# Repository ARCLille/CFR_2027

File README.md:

# CFR_2027
Repo de la coupe de France de Robotique 2027. Cartes électroniques, Firmware et Librairies.

**KiCAD version : 10.0**

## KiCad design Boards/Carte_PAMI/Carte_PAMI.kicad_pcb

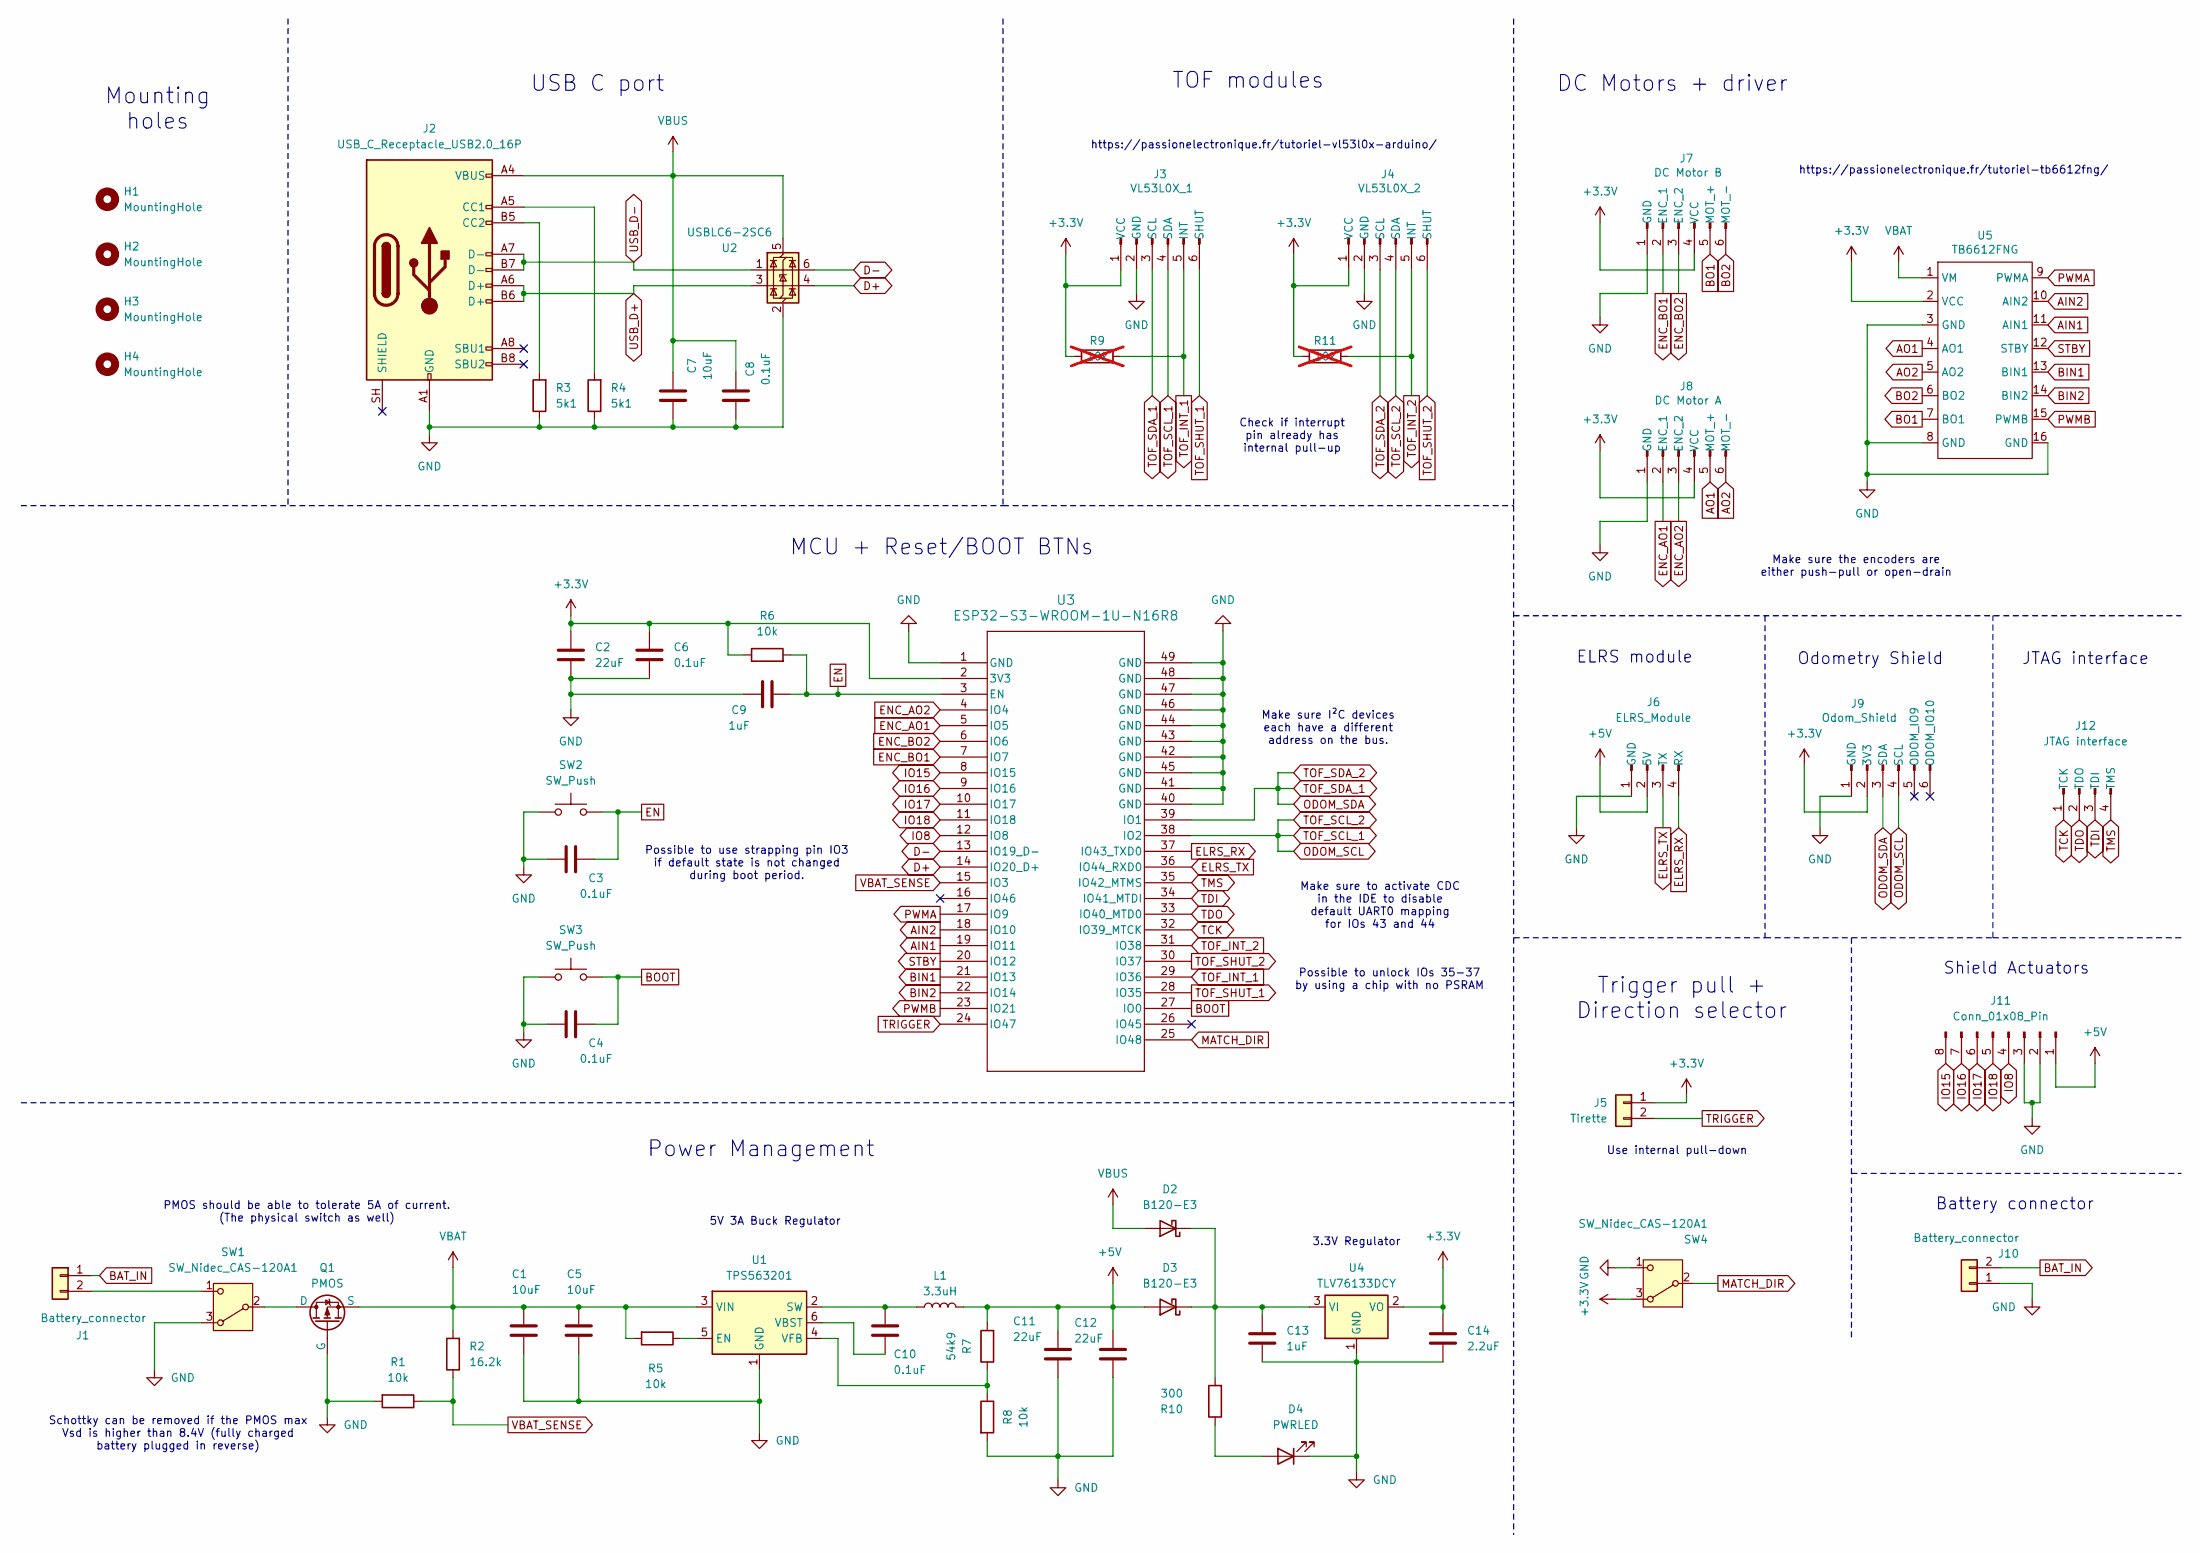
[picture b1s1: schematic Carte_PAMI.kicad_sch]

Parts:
C1, C5: 10uF; C_0805_2012Metric
C2: 22uF; C_1206_3216Metric
C3, C4, C6, C10: 0.1uF; C_0805_2012Metric
C7: 10uF; C_1206_3216Metric
C8: 0.1uF; C_1206_3216Metric
C9, C13: 1uF; C_0805_2012Metric
C11, C12: 22uF; C_0805_2012Metric
C14: 2.2uF; C_0805_2012Metric
D2, D3: B120-E3; D_SMA
D4: PWRLED; LED_1206_3216Metric
H1, H2, H3, H4: MountingHole; MountingHole_2.2mm_M2
J1, J10: Battery_connector; JST_XH_B2B-XH-A_1x02_P2.50mm_Vertical
J2: USB_C_Receptacle_USB2.0_16P; USB_C_Receptacle_GCT_USB4105-xx-A_16P_TopMnt_Horizontal
J3: VL53L0X_1; PinHeader_1x06_P2.54mm_Vertical
J4: VL53L0X_2; PinHeader_1x06_P2.54mm_Vertical
J5: Tirette; JST_XH_B2B-XH-A_1x02_P2.50mm_Vertical
J6: ELRS_Module; PinHeader_1x04_P2.54mm_Vertical
J7: DC Motor B; PinHeader_1x06_P2.54mm_Vertical
J8: DC Motor A; PinHeader_1x06_P2.54mm_Vertical
J9: Odom_Shield; PinHeader_1x06_P2.54mm_Vertical
J11: Conn_01x08_Pin; PinHeader_1x08_P2.54mm_Vertical
J12: JTAG interface; PinHeader_1x04_P2.54mm_Vertical
L1: 3.3uH; L_0805_2012Metric
Q1: PMOS; TO-126-3_Vertical
R1, R5, R6, R8: 10k; R_1206_3216Metric
R2: 16.2k; R_1206_3216Metric
R3, R4: 5k1; R_1206_3216Metric
R7: 54k9; R_1206_3216Metric
R9, R11: 10k; R_1206_3216Metric; not fitted
R10: 300; R_1206_3216Metric
SW1, SW4: SW_Nidec_CAS-120A1; Nidec_Copal_CAS-120A
SW2, SW3: SW_Push; SW_SPST_PTS810
U1: TPS563201; SOT-23-6
U2: USBLC6-2SC6; SOT-23-6
U3: ESP32-S3-WROOM-1U-N16R8; ESP32-S3-WROOM-1U_EXP
U4: TLV76133DCY; SOT-223-3_TabPin2
U5: TB6612FNG; TB6612FNG_socket

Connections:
+3.3V: C2.1, C6.1, C14.1, J3.1 (VCC), J4.1 (VCC), J5.1, J7.4 (VCC), J8.4 (VCC), J9.2 (3V3), R6.1, R9.1, R11.1, SW4.3 (A), U3.2 (3V3), U4.2 (VO), U5.2 (VCC)
+5V: C11.1, C12.1, D3.2 (A), J6.2 (5V), J11.1, L1.2, R7.2
AIN1: U3.19 (IO11), U5.11 (AIN1)
AIN2: U3.18 (IO10), U5.10 (AIN2)
AO1: J8.5 (MOT_+), U5.4 (AO1)
AO2: J8.6 (MOT_-), U5.5 (AO2)
BAT_IN: J1.1, J10.2
BIN1: U3.21 (IO13), U5.13 (BIN1)
BIN2: U3.22 (IO14), U5.14 (BIN2)
BO1: J7.5 (MOT_+), U5.7 (BO1)
BO2: J7.6 (MOT_-), U5.6 (BO2)
BOOT: C4.2, SW3.2, U3.27 (IO0)
D+: U2.4 (I/O2), U3.14 (IO20_D+)
D-: U2.6 (I/O1), U3.13 (IO19_D-)
ELRS_RX: J6.4 (RX), U3.37 (IO43_TXD0)
ELRS_TX: J6.3 (TX), U3.36 (IO44_RXD0)
EN: C3.2, C9.2, R6.2, SW2.2, U3.3 (EN)
ENC_AO1: J8.2 (ENC_1), U3.5 (IO5)
ENC_AO2: J8.3 (ENC_2), U3.4 (IO4)
ENC_BO1: J7.2 (ENC_1), U3.7 (IO7)
ENC_BO2: J7.3 (ENC_2), U3.6 (IO6)
GND: C1.2, C2.2, C3.1, C4.1, C5.2, C6.2, C7.1, C8.1, C9.1, C11.2, C12.2, C13.2, C14.2, D4.1 (K), J2.A1 (GND), J2.A12 (GND), J2.B1 (GND), J2.B12 (GND), J3.2 (GND), J4.2 (GND), J6.1 (GND), J7.1 (GND), J8.1 (GND), J9.1 (GND), J10.1, J11.2, J11.3, Q1.2 (G), R1.2, R3.1, R4.1, R8.2, SW1.3 (A), SW2.1, SW3.1, SW4.1 (C), U1.1 (GND), U2.2 (GND), U3.1 (GND), U3.40 (GND), U3.41 (GND), U3.42 (GND), U3.43 (GND), U3.44 (GND), U3.45 (GND), U3.46 (GND), U3.47 (GND), U3.48 (GND), U3.49 (GND), U4.1 (GND), U5.3 (GND), U5.8 (GND), U5.16 (GND)
IO8: J11.4, U3.12 (IO8)
IO15: J11.8, U3.8 (IO15)
IO16: J11.7, U3.9 (IO16)
IO17: J11.6, U3.10 (IO17)
IO18: J11.5, U3.11 (IO18)
MATCH_DIR: SW4.2 (B), U3.25 (IO48)
unnamed: C13.1, D2.1 (K), D3.1 (K), R10.2, U4.3 (VI)
unnamed: D4.2 (A), R10.1
unnamed: J1.2, SW1.1 (C)
unnamed: J2.A5 (CC1), R4.2
unnamed: J2.B5 (CC2), R3.2
unnamed: Q1.1 (D), SW1.2 (B)
unnamed: R5.1, U1.5 (EN)
unnamed: C10.1, L1.1, U1.2 (SW)
unnamed: C10.2, U1.6 (VBST)
unnamed: R7.1, R8.1, U1.4 (VFB)
ODOM_SCL: J3.4 (SDA), J4.4 (SDA), J9.4 (SCL), U3.38 (IO2)
ODOM_SDA: J3.3 (SCL), J4.3 (SCL), J9.3 (SDA), U3.39 (IO1)
PWMA: U3.17 (IO9), U5.9 (PWMA)
PWMB: U3.23 (IO21), U5.15 (PWMB)
STBY: U3.20 (IO12), U5.12 (STBY)
TCK: J12.1 (TCK), U3.32 (IO39_MTCK)
TDI: J12.3 (TDI), U3.34 (IO41_MTDI)
TDO: J12.2 (TDO), U3.33 (IO40_MTD0)
TMS: J12.4 (TMS), U3.35 (IO42_MTMS)
TOF_INT_1: J3.5 (INT), R9.2, U3.29 (IO36)
TOF_INT_2: J4.5 (INT), R11.2, U3.31 (IO38)
TOF_SHUT_1: J3.6 (SHUT), U3.28 (IO35)
TOF_SHUT_2: J4.6 (SHUT), U3.30 (IO37)
TRIGGER: J5.2, U3.24 (IO47)
USB_D+: J2.A6 (D+), J2.B6 (D+), U2.3 (I/O2)
USB_D-: J2.A7 (D-), J2.B7 (D-), U2.1 (I/O1)
VBAT: C1.1, C5.1, Q1.3 (S), R2.2, R5.2, U1.3 (VIN), U5.1 (VM)
VBAT_SENSE: R1.1, R2.1, U3.15 (IO3)
VBUS: C7.2, C8.2, D2.2 (A), J2.A4 (VBUS), J2.A9 (VBUS), J2.B4 (VBUS), J2.B9 (VBUS), U2.5 (VBUS)

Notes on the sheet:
Make sure I²C devices each have a different address on the bus.
USB C port
Trigger pull + Direction selector
Make sure the encoders are either push-pull or open-drain
5V 3A Buck Regulator
JTAG interface
DC Motors + driver
3.3V Regulator
Power Management
Possible to use strapping pin IO3 if default state is not changed during boot period.
MCU + Reset/BOOT BTNs
Shield Actuators
https://passionelectronique.fr/tutoriel-tb6612fng/
Odometry Shield
Mounting holes
Battery connector
ELRS module
PMOS should be able to tolerate 5A of current. (The physical switch as well)
https://passionelectronique.fr/tutoriel-vl53l0x-arduino/
Possible to unlock IOs 35-37 by using a chip with no PSRAM
Schottky can be removed if the PMOS max Vsd is higher than 8.4V (fully charged battery plugged in reverse)
Make sure to activate CDC in the IDE to disable default UART0 mapping for IOs 43 and 44
Check if interrupt pin already has internal pull-up
TOF modules
Use internal pull-down

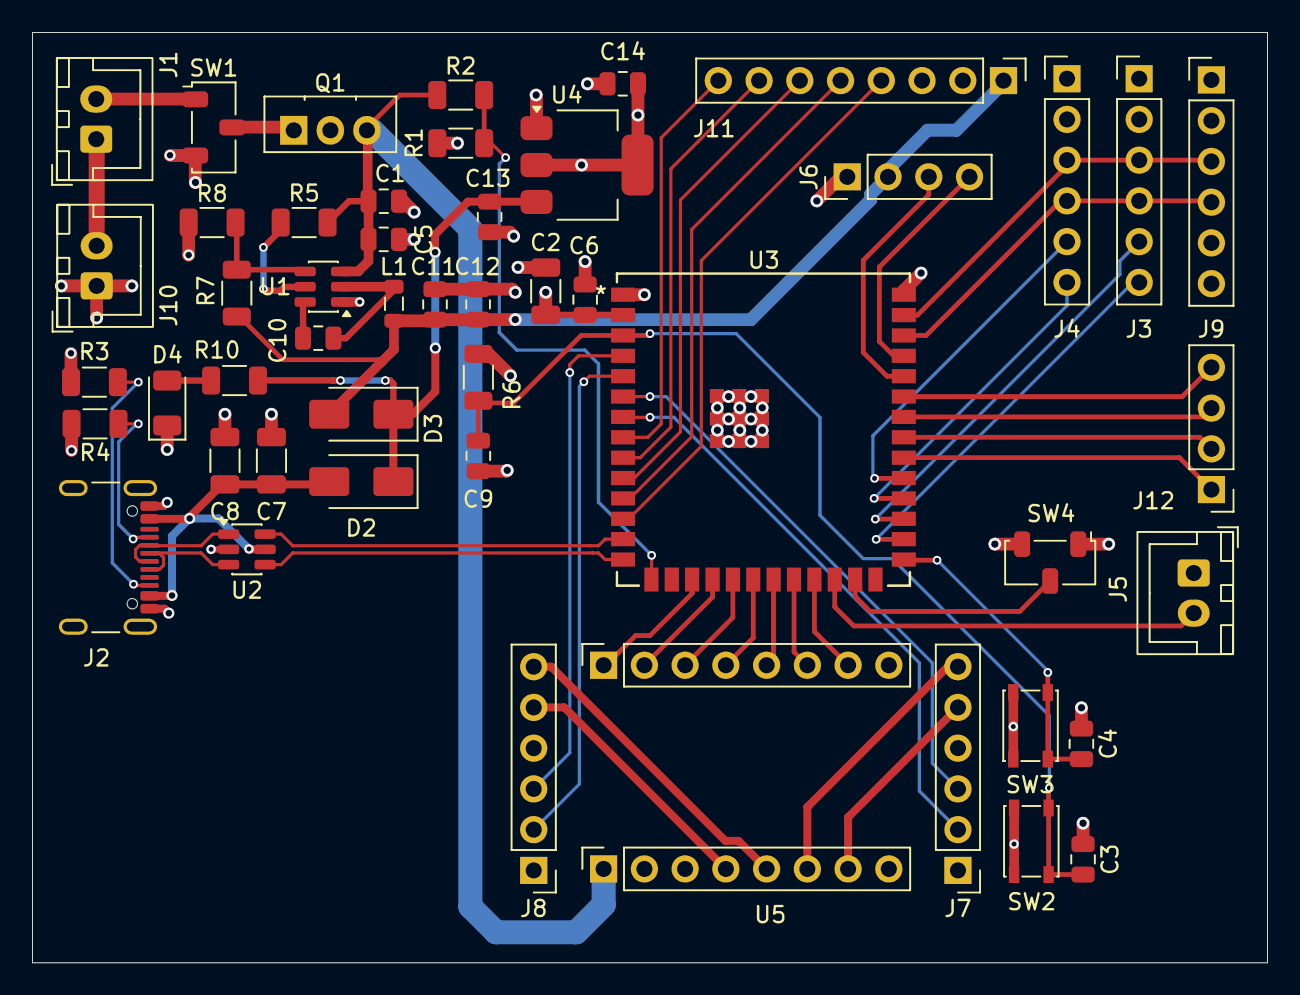
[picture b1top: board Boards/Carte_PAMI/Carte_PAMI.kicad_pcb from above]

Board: 4 copper layers, 77.0 x 58.0 mm, 53 parts (0 on the bottom side), 57 nets.

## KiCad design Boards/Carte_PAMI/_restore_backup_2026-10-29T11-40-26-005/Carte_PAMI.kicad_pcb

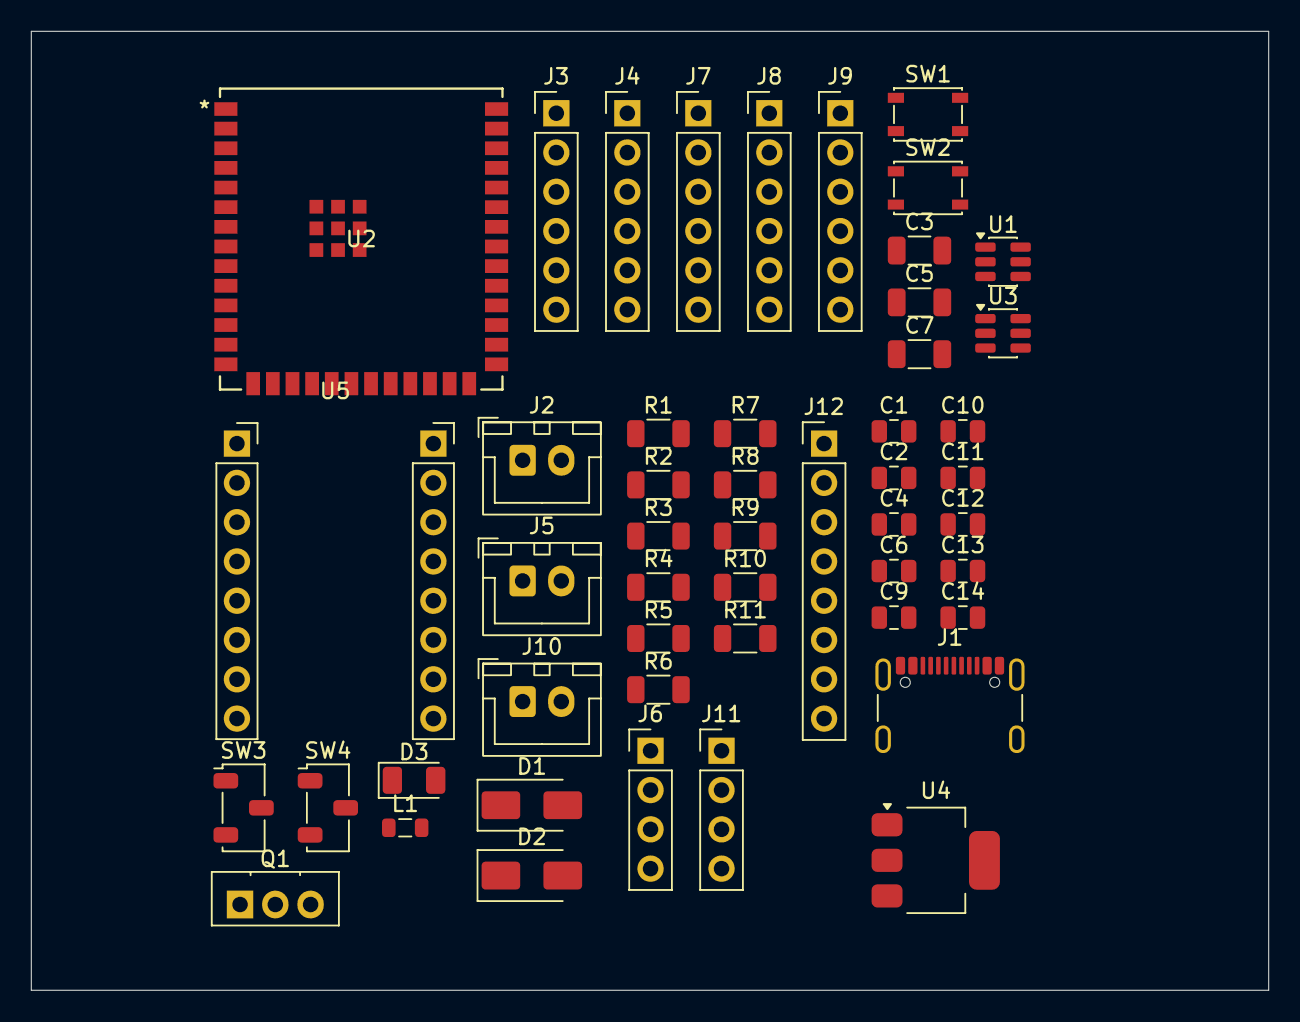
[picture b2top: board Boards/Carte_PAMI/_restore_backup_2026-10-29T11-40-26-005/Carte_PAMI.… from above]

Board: 4 copper layers, 80.0 x 62.0 mm, 50 parts (0 on the bottom side), 57 nets, no tracks yet.

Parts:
C1, C2, C4, C14: 0.1uF; C_0805_2012Metric
C3: 22uF; C_1206_3216Metric
C5: 10uF; C_1206_3216Metric
C6: 1uF; C_0805_2012Metric
C7: 0.1uF; C_1206_3216Metric
C9, C11: 10uF; C_0805_2012Metric
C10: 2.2uF; C_0805_2012Metric
C12, C13: 22uF; C_0805_2012Metric
D1, D2: B120-E3; D_SMA
D3: PWRLED; LED_1206_3216Metric
J1: USB_C_Receptacle_USB2.0_16P; USB_C_Receptacle_GCT_USB4105-xx-A_16P_TopMnt_Horizontal
J2, J10: Battery_connector; JST_XH_B2B-XH-A_1x02_P2.50mm_Vertical
J3: VL53L0X_1; PinHeader_1x06_P2.54mm_Vertical
J4: VL53L0X_2; PinHeader_1x06_P2.54mm_Vertical
J5: Tirette; JST_XH_B2B-XH-A_1x02_P2.50mm_Vertical
J6: ELRS_Module; PinHeader_1x04_P2.54mm_Vertical
J7: DC Motor B; PinHeader_1x06_P2.54mm_Vertical
J8: DC Motor A; PinHeader_1x06_P2.54mm_Vertical
J9: Odom_Shield; PinHeader_1x06_P2.54mm_Vertical
J11: JTAG interface; PinHeader_1x04_P2.54mm_Vertical
J12: Conn_01x08_Pin; PinHeader_1x08_P2.54mm_Vertical
L1: 2.2uH; L_0805_2012Metric
Q1: PMOS; TO-126-3_Vertical
R1, R2, R3, R5, R6, R8, R9: 10k; R_1206_3216Metric
R4: 16.2k; R_1206_3216Metric
R7: 300; R_1206_3216Metric
R10: 12k4; R_1206_3216Metric
R11: 2k21; R_1206_3216Metric
SW1, SW2: SW_Push; SW_SPST_PTS810
SW3, SW4: SW_Nidec_CAS-120A1; Nidec_Copal_CAS-120A
U1: USBLC6-2SC6; SOT-23-6
U2: ESP32-S3-WROOM-1U-N16R8; ESP32-S3-WROOM-1U_EXP
U3: TPS563201; SOT-23-6
U4: TLV76133DCY; SOT-223-3_TabPin2
U5: TB6612FNG; TB6612FNG_socket

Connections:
+3.3V: C3.1, C4.1, C10.1, J3.1 (VCC), J4.1 (VCC), J5.1, J7.4 (VCC), J8.4 (VCC), J9.2 (3V3), R3.1, R6.1, R8.1, SW3.3 (A), U2.2 (3V3), U4.2 (VO), U5.2 (VCC)
+5V: C5.2, C7.2, C12.1, C13.1, D1.1 (K), J6.2 (5V), J12.1, L1.2, R7.2, R10.2, U1.5 (VBUS), U4.3 (VI)
AIN1: U2.19 (IO11), U5.11 (AIN1)
AIN2: U2.18 (IO10), U5.10 (AIN2)
AO1: J8.5 (MOT_+), U5.4 (AO1)
AO2: J8.6 (MOT_-), U5.5 (AO2)
BAT_IN: J2.2, J10.2
BIN1: U2.21 (IO13), U5.13 (BIN1)
BIN2: U2.22 (IO14), U5.14 (BIN2)
BO1: J7.5 (MOT_+), U5.7 (BO1)
BO2: J7.6 (MOT_-), U5.6 (BO2)
BOOT: C2.2, SW2.2, U2.27 (IO0)
D+: U1.4 (I/O2), U2.14 (IO20_D+)
D-: U1.6 (I/O1), U2.13 (IO19_D-)
ELRS_RX: J6.4 (RX), U2.37 (IO43_TXD0)
ELRS_TX: J6.3 (TX), U2.36 (IO44_RXD0)
EN: C1.2, C6.2, R3.2, SW1.2, U2.3 (EN)
ENC_AO1: J8.2 (ENC_1), U2.5 (IO5)
ENC_AO2: J8.3 (ENC_2), U2.4 (IO4)
ENC_BO1: J7.2 (ENC_1), U2.7 (IO7)
ENC_BO2: J7.3 (ENC_2), U2.6 (IO6)
GND: C1.1, C2.1, C3.2, C4.2, C5.1, C6.1, C7.1, C9.2, C10.2, C11.2, D3.1 (K), J1.A1 (GND), J1.A12 (GND), J1.B1 (GND), J1.B12 (GND), J3.2 (GND), J4.2 (GND), J6.1 (GND), J7.1 (GND), J8.1 (GND), J9.1 (GND), J10.1, J12.2, J12.3, Q1.2 (G), R1.1, R2.1, R5.2, SW1.1, SW2.1, SW3.1 (C), SW4.3 (A), U1.2 (GND), U2.1 (GND), U2.40 (GND), U2.41 (GND), U2.42 (GND), U2.43 (GND), U2.44 (GND), U2.45 (GND), U2.46 (GND), U2.47 (GND), U2.48 (GND), U2.49 (GND), U3.1 (GND), U4.1 (GND), U5.3 (GND), U5.8 (GND), U5.16 (GND)
IO8: J12.4, U2.12 (IO8)
IO15: J12.8, U2.8 (IO15)
IO16: J12.7, U2.9 (IO16)
IO17: J12.6, U2.10 (IO17)
IO18: J12.5, U2.11 (IO18)
MATCH_DIR: SW3.2 (B), U2.25 (IO48)
unnamed: D1.2 (A), J1.A4 (VBUS), J1.A9 (VBUS), J1.B4 (VBUS), J1.B9 (VBUS)
unnamed: D2.2 (A), Q1.3 (S)
unnamed: C12.2, C13.2, D3.2 (A), R7.1, R11.2
unnamed: J1.A5 (CC1), R2.2
unnamed: J1.B5 (CC2), R1.2
unnamed: J1.A6 (D+), J1.B6 (D+), U1.3 (I/O2)
unnamed: J1.A7 (D-), J1.B7 (D-), U1.1 (I/O1)
unnamed: J2.1, SW4.1 (C)
unnamed: Q1.1 (D), SW4.2 (B)
unnamed: R9.1, U3.5 (EN)
unnamed: C14.1, L1.1, U3.2 (SW)
unnamed: C14.2, U3.6 (VBST)
unnamed: R10.1, R11.1, U3.4 (VFB)
ODOM_SCL: J3.4 (SDA), J4.4 (SDA), J9.4 (SCL), U2.38 (IO2)
ODOM_SDA: J3.3 (SCL), J4.3 (SCL), J9.3 (SDA), U2.39 (IO1)
PWMA: U2.17 (IO9), U5.9 (PWMA)
PWMB: U2.23 (IO21), U5.15 (PWMB)
STBY: U2.20 (IO12), U5.12 (STBY)
TCK: J11.1 (TCK), U2.32 (IO39_MTCK)
TDI: J11.2 (TDI), U2.34 (IO41_MTDI)
TDO: J11.3 (TDO), U2.33 (IO40_MTD0)
TMS: J11.4 (TMS), U2.35 (IO42_MTMS)
TOF_INT_1: J3.5 (INT), R6.2, U2.28 (IO35)
TOF_INT_2: J4.5 (INT), R8.2, U2.29 (IO36)
TOF_SHUT_1: J3.6 (SHUT), U2.30 (IO37)
TOF_SHUT_2: J4.6 (SHUT), U2.31 (IO38)
TRIGGER: J5.2, U2.24 (IO47)
VBAT: C9.1, C11.1, D2.1 (K), R4.2, R9.2, U3.3 (VIN), U5.1 (VM)
VBAT_SENSE: R4.1, R5.1, U2.15 (IO3)

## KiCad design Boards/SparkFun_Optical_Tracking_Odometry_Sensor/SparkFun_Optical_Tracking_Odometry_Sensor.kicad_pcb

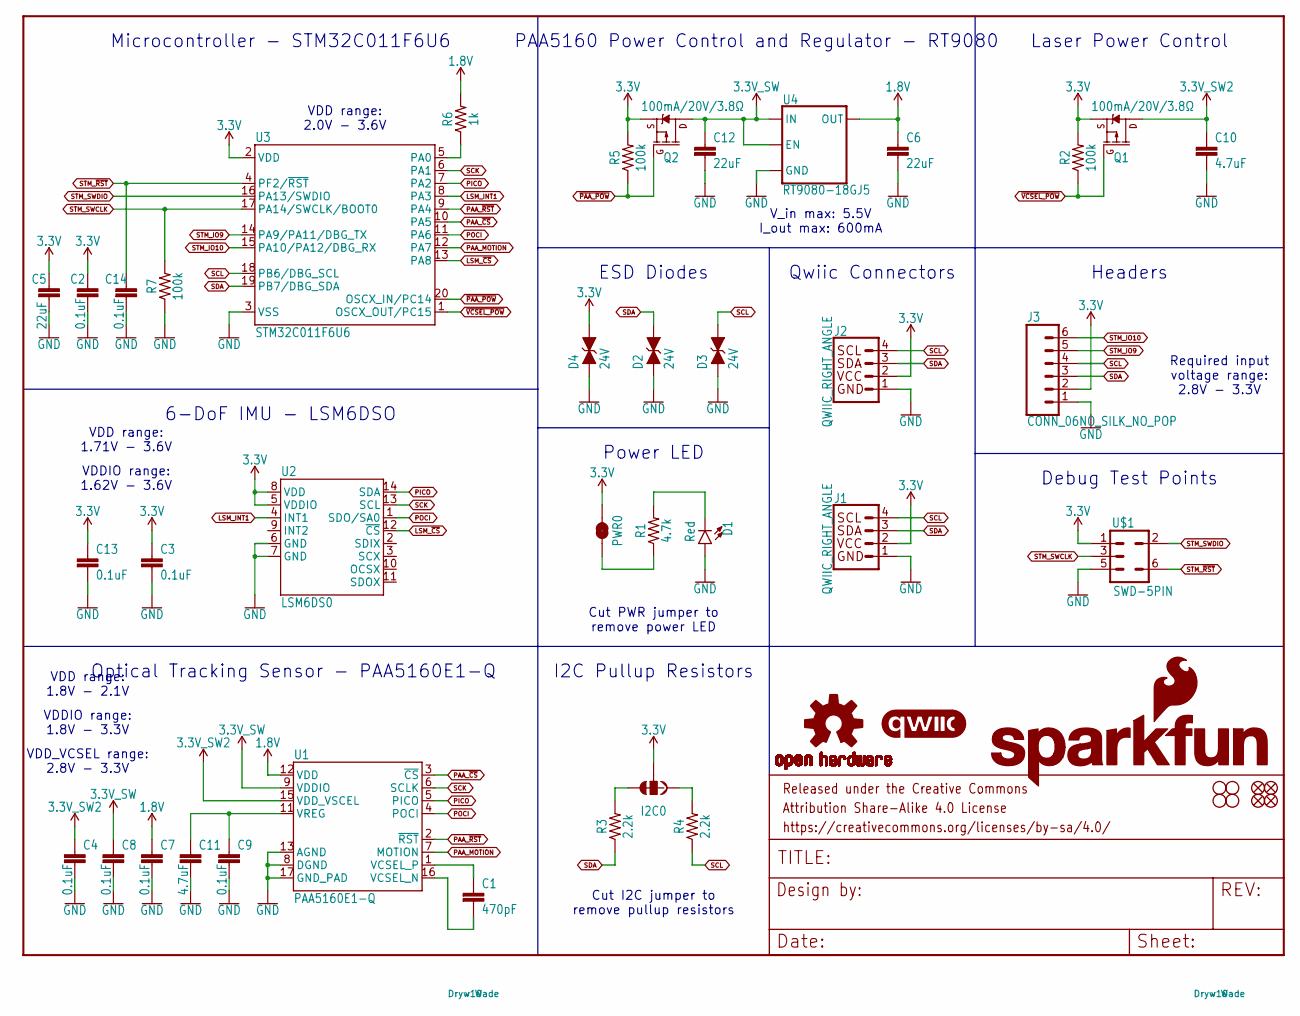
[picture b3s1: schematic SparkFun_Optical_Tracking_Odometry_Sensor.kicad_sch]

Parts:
C1: 470pF; 0603
C2, C3, C4, C7, C8, C9, C13, C14: 0.1uF; 0603
C5, C6, C12: 22uF; 0603
C10, C11: 4.7uF; 0603
D1: Red; LED-0603
D2, D3, D4: 24V; 0603
FD1, FD2, FD3, FD4: FIDUCIAL1X2; FIDUCIAL-1X2
FRAME1: FRAME-LETTER; CREATIVE_COMMONS
H1, H2, H3, H4: STAND-OFF
I2C0: JUMPER-SMT_3_2-NC_TRACE_SILK; SMT-JUMPER_3_2-NC_TRACE_SILK
J1, J2: QWIIC_RIGHT_ANGLE; JST04_1MM_RA
J3: CONN_06NO_SILK_NO_POP; 1X06_NO_SILK
LOGO1: OSHW-LOGOS; OSHW-LOGO-S
LOGO2: QWIIC_LOGO_5MM; QWIIC_5MM
LOGO3: SFE_LOGO_NAME_FLAME.1_INCH; SFE_LOGO_NAME_FLAME_.1
PWR0: JUMPER-SMT_2_NC_TRACE_SILK; SMT-JUMPER_2_NC_TRACE_SILK
Q1, Q2: 100mA/20V/3.8Ω; SOT-416FL
R1: 4.7k; 0603
R2, R5, R7: 100k; 0603
R3, R4: 2.2k; 0603
R6: 1k; 0603
U1: PAA5160E1-Q
U2: LSM6DS0; LGA14L
U3: STM32C011F6U6
U4: RT9080-18GJ5; SOT23-5
U$1: SWD-5PIN; PAD_05_03X2_TP_NO4

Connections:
1.8V: C6.1, C7.1, R6.2, U1.12 (VDD), U4.5 (OUT)
3.3V: C2.1, C3.1, C5.1, C13.1, D4.2 (C), I2C0.2, J1.2, J2.2, J3.2, PWR0.2, Q1.2 (S), Q2.2 (S), R2.2, R5.2, U2.5 (VDDIO), U2.8 (VDD), U3.2 (VDD), U$1.1
3.3V_SW: C8.1, C12.1, Q2.3 (D), U1.9 (VDDIO), U4.1 (IN), U4.3 (EN)
3.3V_SW2: C4.1, C10.1, Q1.3 (D), U1.15 (VDD_VSCEL)
GND: C2.2, C3.2, C4.2, C5.2, C6.2, C7.2, C8.2, C9.2, C10.2, C11.2, C12.2, C13.2, C14.2, D1.A, D2.1 (A), D3.1 (A), D4.1 (A), J1.1, J2.1, J3.1, R7.1, U1.8 (DGND), U1.13 (AGND), U1.17 (GND_PAD), U2.6 (GND), U2.7 (GND), U3.3 (VSS), U4.2 (GND), U$1.5
LSM_INT1: U2.4 (INT1), U3.8 (PA3)
LSM_~CS: U2.12 (~CS), U3.13 (PA8)
unnamed: PWR0.1, R1.1
unnamed: D1.C, R1.2
unnamed: C1.1, U1.1 (VCSEL_P)
unnamed: C1.2, U1.16 (VCSEL_N)
unnamed: I2C0.3, R3.2
unnamed: I2C0.1, R4.2
unnamed: C9.1, C11.1, U1.11 (VREG)
unnamed: R6.1, U3.5 (PA0)
PAA_MOTION: U1.7 (MOTION), U3.12 (PA7)
PAA_~CS: U1.3 (~CS), U3.10 (PA5)
PAA_~RST: U1.2 (~RST), U3.9 (PA4)
PICO: U1.5 (PICO), U2.14 (SDA), U3.7 (PA2)
POCI: U1.4 (POCI), U2.1 (SDO/SA0), U3.11 (PA6)
SCK: U1.6 (SCLK), U2.13 (SCL), U3.6 (PA1)
SCL: D3.2 (C), J1.4, J2.4, J3.4, R4.1, U3.18 (PB6/DBG_SCL)
SDA: D2.2 (C), J1.3, J2.3, J3.3, R3.1, U3.19 (PB7/DBG_SDA)
STM_IO9: J3.5, U3.14 (PA9/PA11/DBG_TX)
STM_IO10: J3.6, U3.15 (PA10/PA12/DBG_RX)
STM_SWCLK: R7.2, U3.17 (PA14/SWCLK/BOOT0), U$1.3
STM_SWDIO: U3.16 (PA13/SWDIO), U$1.2
STM_~RST: C14.1, U3.4 (PF2/~RST), U$1.6
~PAA_POW: Q2.1 (G), R5.1, U3.20 (OSCX_IN/PC14)
~VCSEL_POW: Q1.1 (G), R2.1, U3.1 (OSCX_OUT/PC15)

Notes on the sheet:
Cut PWR jumper to remove power LED
VDD range: 2.0V - 3.6V
I2C Pullup Resistors
VDD range: 1.71V - 3.6V
Laser Power Control
VDD range: 1.8V - 2.1V
Debug Test Points
Power LED
VDDIO range: 1.8V - 3.3V
VDDIO range: 1.62V - 3.6V
V_in max: 5.5V I_out max: 600mA
Required input voltage range: 2.8V - 3.3V
Cut I2C jumper to remove pullup resistors
6-DoF IMU - LSM6DSO
Optical Tracking Sensor - PAA5160E1-Q
VDD_VCSEL range: 2.8V - 3.3V
Microcontroller - STM32C011F6U6
PAA5160 Power Control and Regulator - RT9080
ESD Diodes
Headers
Qwiic Connectors

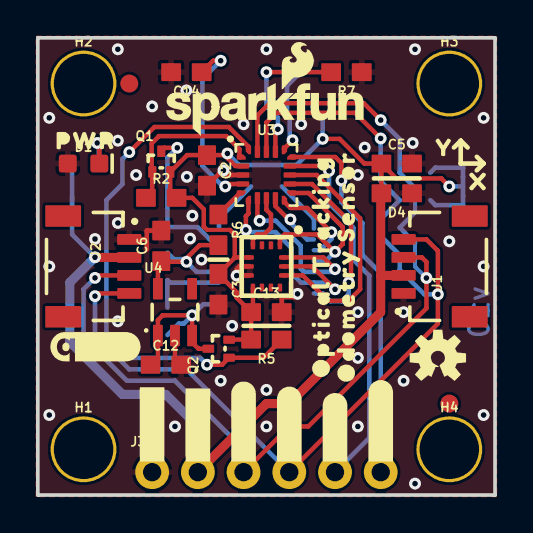
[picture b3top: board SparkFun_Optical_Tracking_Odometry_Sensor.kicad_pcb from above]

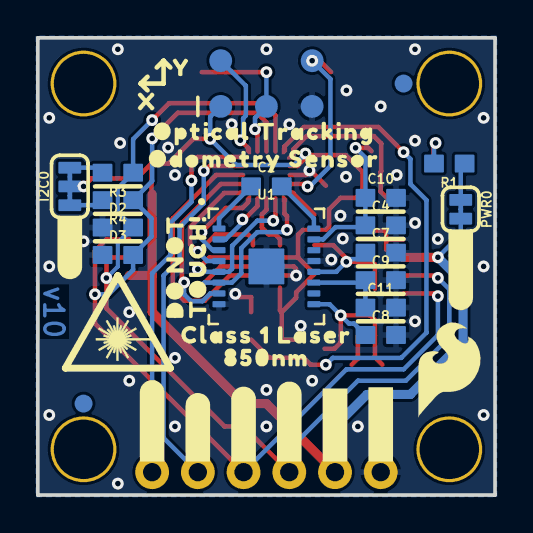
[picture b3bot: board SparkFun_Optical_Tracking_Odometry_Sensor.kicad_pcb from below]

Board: 2 copper layers, 25.4 x 25.4 mm, 78 parts (35 on the bottom side), 30 nets.

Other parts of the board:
U$2, U$8: #_GND#0
U$3, U$9: #_3V3#0
U$4, U$10: #_SDA#0
U$5, U$11: #_SCL#0
U$6: CLASS_1_LASER0
U$7, U$23: #_IO10#0
U$12, U$32: #_IO9#0
U$14, U$16: OPTICAL_TRACKING0
U$15, U$17: ODOMETRY_SENSOR0
U$18, U$30: X0
U$20: #PWR#0
U$21: TOUCH##0
U$22: DO_NOT0
U$24: SFE_LOGO_FLAME_.2
U$25: PWR0
U$26: #I2C#0
U$27: ORDERING_INSTRUCTIONS
U$28: 850NM0
U$29, U$31: Y0

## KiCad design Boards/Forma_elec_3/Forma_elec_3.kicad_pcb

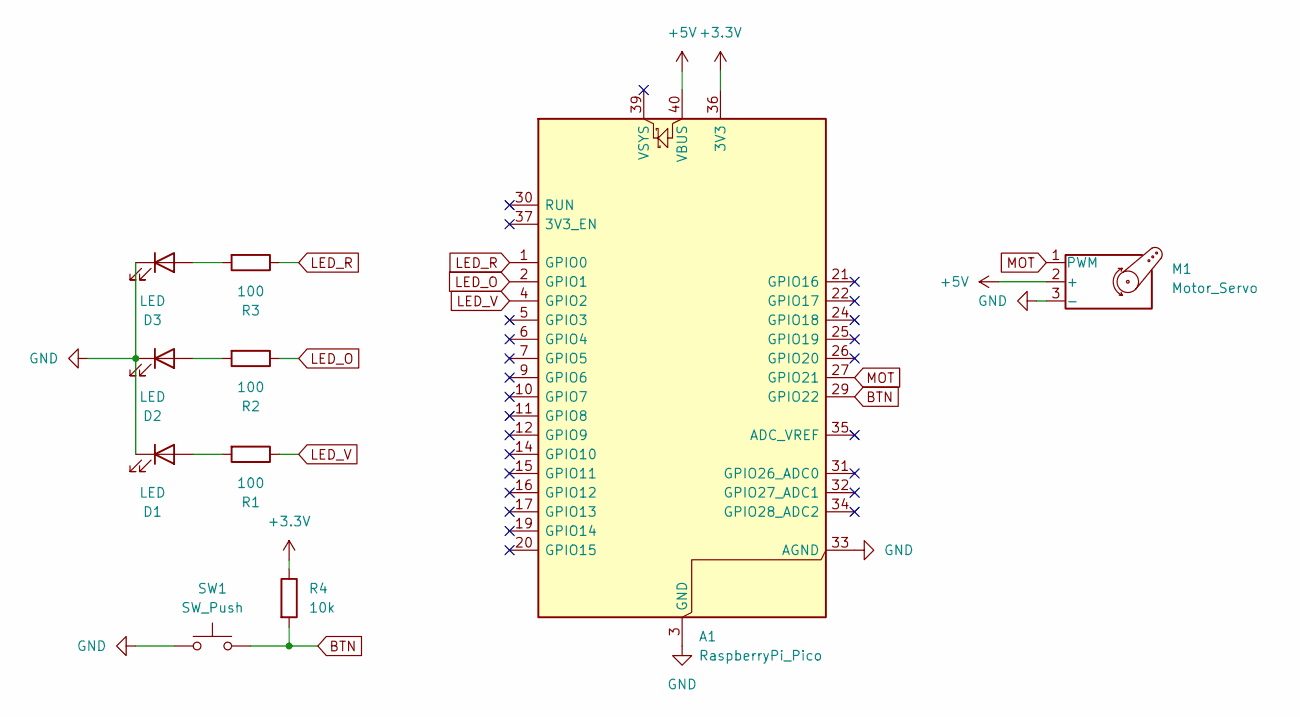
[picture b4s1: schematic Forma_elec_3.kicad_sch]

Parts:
A1: RaspberryPi_Pico; RaspberryPi_Pico_Common_Unspecified
D1, D2, D3: LED; LED_D5.0mm
M1: Motor_Servo; PinHeader_1x03_P2.54mm_Vertical
R1, R2, R3: 100; R_1206_3216Metric
R4: 10k; R_1206_3216Metric
SW1: SW_Push; SW_PUSH_6mm_H4.3mm

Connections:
+3.3V: A1.36 (3V3), R4.1
+5V: A1.40 (VBUS), M1.2 (+)
BTN: A1.29 (GPIO22), R4.2, SW1.2
GND: A1.3 (GND), A1.8 (GND), A1.13 (GND), A1.18 (GND), A1.23 (GND), A1.28 (GND), A1.33 (AGND), A1.38 (GND), D1.1 (K), D2.1 (K), D3.1 (K), M1.3 (-), SW1.1
LED_O: A1.2 (GPIO1), R2.1
LED_R: A1.1 (GPIO0), R3.1
LED_V: A1.4 (GPIO2), R1.1
MOT: A1.27 (GPIO21), M1.1 (PWM)
unnamed: D1.2 (A), R1.2
unnamed: D2.2 (A), R2.2
unnamed: D3.2 (A), R3.2

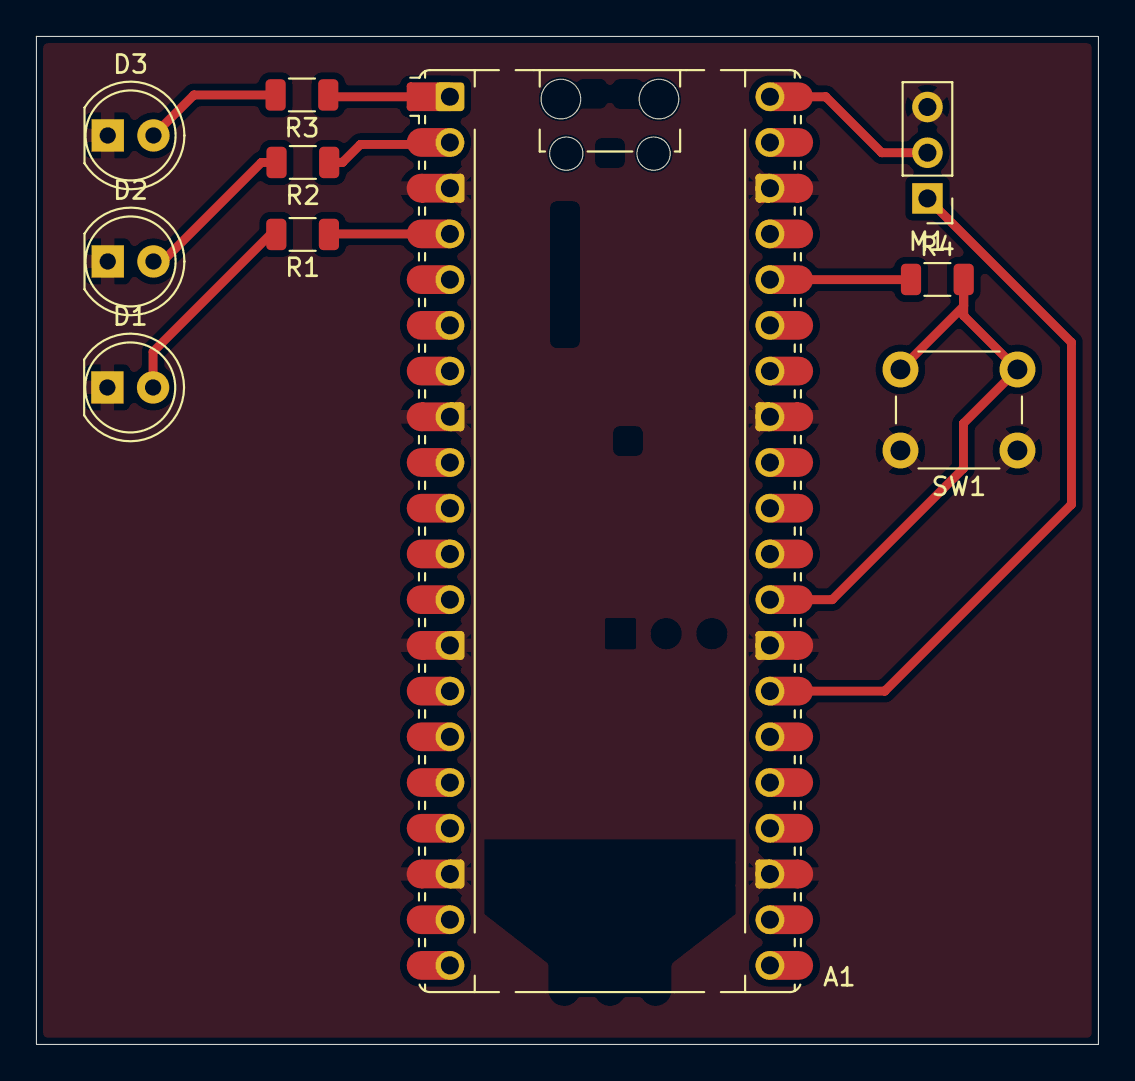
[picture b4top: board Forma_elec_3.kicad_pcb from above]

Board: 2 copper layers, 59.0 x 56.0 mm, 10 parts (0 on the bottom side), 11 nets.

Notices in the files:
Boards/SparkFun_Optical_Tracking_Odometry_Sensor/SparkFun_Optical_Tracking_Odometry_Sensor.kicad_sch:
Released under the Creative Commons
https://creativecommons.org/licenses/by-sa/4.0
parts and their libraries:
Released under the Creative Commons Attribution Share-Alike 4.0 License
